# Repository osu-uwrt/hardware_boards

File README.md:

# riptide_hardware
Riptide specific EAGLE libs and board files

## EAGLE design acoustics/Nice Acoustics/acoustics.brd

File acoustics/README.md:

# riptide_hardware
Acoustics board.

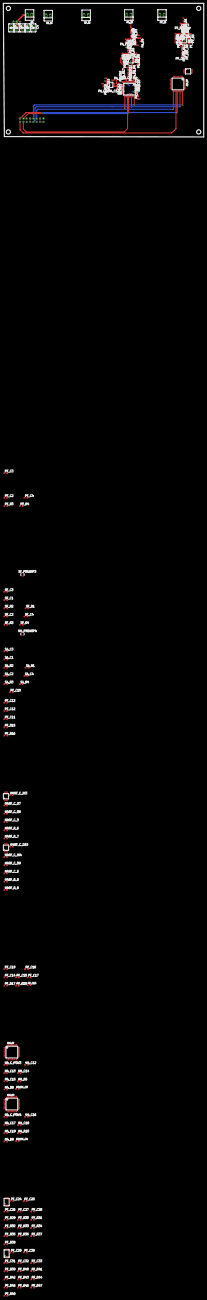
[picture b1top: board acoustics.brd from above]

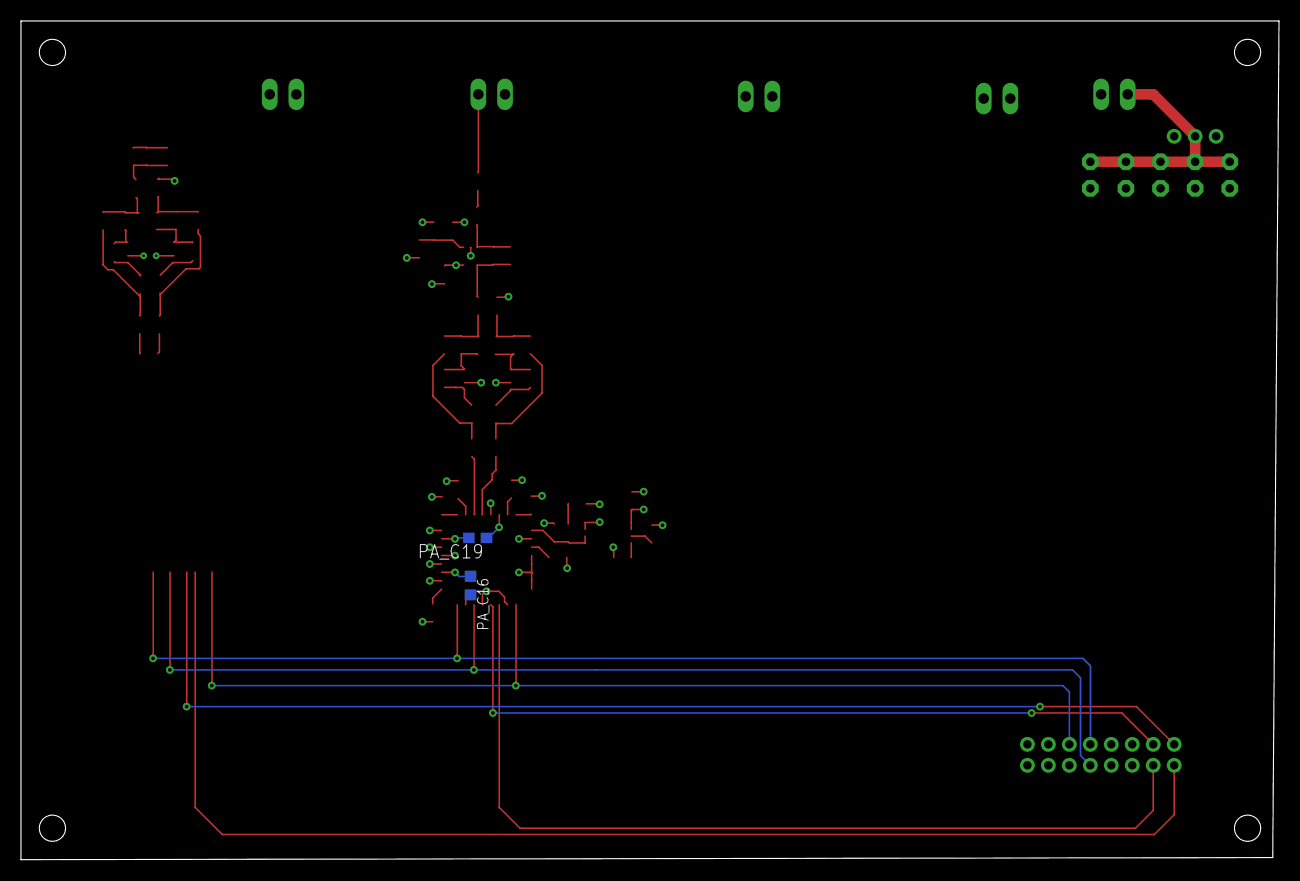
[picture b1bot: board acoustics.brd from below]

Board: 4 copper layers, 120.0 x 80.0 mm, 176 parts (2 on the bottom side), 114 nets.

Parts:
ADC_H7, ADC_H8: ADS8322; TQFP-32
ADC_PA: ADS8322; TQFP-32
ADC_PF: ADS8322; TQFP-32
C1, C2, C3, C4, C5: C2.5-3
H4ADC_C3, H4ADC_C4: 1uf; C0603K
H4RF_C_3, H4RF_C_5, H4_C12, H4_C13, H4_C14, H4_C15, H4_C16, H4_C17, H4_C18, H4_C19, H4_C_POW3, H4_C_POW4: 1uf; C0603
H4RF_C_IN3, H4RF_C_IN4: 10uf; C0603
H4RF_C_O7, H4RF_C_O9: 0.1uf; C0603
H4RF_C_O8, H4RF_C_O10: 47uf; C0603
H4RF_R_6, H4RF_R_8: 121k; R0603
H4RF_R_7, H4RF_R_9: 47m; R0603
H4_PREAMP4: TLV6741; SC70-5
H4_R5, H4_R9: 60.4k; R0603
H4_R8, H4_R10: 10K; R0603
H4_REFGEN3, H4_REFGEN4: REF6025
P1: 22-23-2021
PA_C1: 1pF; C0603
PA_C2: 5nF; C0603
PA_C3: 10mF; C0603
PA_C4: 100nF; C0603
PA_C5, PA_C9: 270pF; C0603
PA_C6: 470 pF; C0603
PA_C7: 1nF; C0603
PA_C8: 22nF; C0603
PA_C10: 10uf; C0603
PA_C11, PA_C14, PA_C15, PA_C17, PA_C18, PA_C19: 1uf; C0603
PA_C12: 47uf; C0603
PA_C13: 0.1uf; C0603
PA_C16: 1uf; C0603K
PA_DA: THS4551; VSSOP-8
PA_IN: 22-23-2021
PA_PREAMP: TLV6741; SC70-5
PA_R1: 10k; R0603
PA_R2: 1 M; R0603
PA_R3, PA_R4: 100k; R0603
PA_R5, PA_R10, PA_R14: 1.2k; R0603
PA_R6: 1.2K; R0603
PA_R7, PA_R11: 330; R0603
PA_R8, PA_R12: 5; R0603
PA_R9, PA_R13: 10; R0603
PA_R15: 121k; R0603
PA_R16: 47m; R0603
PA_R17: 60.4k; R0603
PA_R18: 10K; R0603
PA_REFGEN: REF6025
PF_C1: 1pF; C0603
PF_C2: 5nF; C0603
PF_C3: 10mF; C0603
PF_C4: 100nF; C0603
PF_C5, PF_C9, PF_C24, PF_C25, PF_C29, PF_C30: 270pF; C0603
PF_C6, PF_C27, PF_C32: 470 pF; C0603
PF_C7, PF_C26, PF_C31: 1nF; C0603
PF_C8, PF_C28, PF_C33: 22nF; C0603
PF_C10: 10uf; C0603
PF_C11, PF_C14, PF_C15, PF_C17, PF_C18, PF_C19: 1uf; C0603
PF_C12: 47uf; C0603
PF_C13: 0.1uf; C0603
PF_C16: 1uf; C0603K
PF_DA, PF_DA2, PF_DA3: THS4551; VSSOP-8
PF_IN: 22-23-2021
PF_PREAMP: TLV6741; SC70-5
PF_R1: 10k; R0603
PF_R2: 1 M; R0603
PF_R3, PF_R4: 100k; R0603
PF_R5, PF_R10, PF_R14, PF_R31, PF_R35, PF_R36, PF_R41, PF_R45, PF_R46: 1.2k; R0603
PF_R6, PF_R30, PF_R40: 1.2K; R0603
PF_R7, PF_R11, PF_R29, PF_R32, PF_R39, PF_R42: 330; R0603
PF_R8, PF_R12, PF_R33, PF_R34, PF_R43, PF_R44: 5; R0603
PF_R9, PF_R13, PF_R37, PF_R38, PF_R47, PF_R48: 10; R0603
PF_R15: 121k; R0603
PF_R16: 47m; R0603
PF_R17: 60.4k; R0603
PF_R18: 10K; R0603
PF_REFGEN: REF6025
SA_C1: 1pF; C0603
SA_C2: 5nF; C0603
SA_C3: 10mF; C0603
SA_C4: 100nF; C0603
SA_IN: 22-23-2021
SA_R1: 10k; R0603
SA_R2: 1 M; R0603
SA_R3, SA_R4: 100k; R0603
SF_C1: 1pF; C0603
SF_C2: 5nF; C0603
SF_C3: 10mF; C0603
SF_C4: 100nF; C0603
SF_IN: 22-23-2021
SF_PREAMP3: TLV6741; SC70-5
SF_R1: 10k; R0603
SF_R2: 1 M; R0603
SF_R3, SF_R4: 100k; R0603
U$1: 1X3
U$2: 2X8

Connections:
+3V3: ADC_H7.6, ADC_H7.27, ADC_H7.28, ADC_H7.29, ADC_H7.32, ADC_H8.6, ADC_H8.27, ADC_H8.28, ADC_H8.29, ADC_H8.32, ADC_PA.6, ADC_PA.27, ADC_PA.28, ADC_PA.29, ADC_PA.32, ADC_PF.6, ADC_PF.27, ADC_PF.28, ADC_PF.29, ADC_PF.32, H4ADC_C3.1, H4ADC_C4.1, H4RF_C_IN3.2, H4RF_C_IN4.2, H4_C_POW3.1, H4_C_POW4.1, H4_PREAMP4.5, H4_REFGEN3.1, H4_REFGEN3.2, H4_REFGEN4.1, H4_REFGEN4.2, PA_C4.2, PA_C10.2, PA_C16.1, PA_C19.1, PA_DA.3, PA_PREAMP.5, PA_R4.2, PA_REFGEN.1, PA_REFGEN.2, PF_C4.2, PF_C10.2, PF_C16.1, PF_C19.1, PF_DA.3, PF_DA2.3, PF_DA3.3, PF_PREAMP.5, PF_R4.2, PF_REFGEN.1, PF_REFGEN.2, SA_C4.2, SA_R4.2, SF_C4.2, SF_PREAMP3.5, SF_R4.2, U$1.1
+5V: C1.1, C2.1, C3.1, C4.1, C5.1, P1.2, U$1.2
AMPED_PA: PA_C1.2, PA_PREAMP.4, PA_R2.2, PA_R6.1
AMPED_PF: PF_C1.2, PF_PREAMP.4, PF_R2.2, PF_R6.1
AMPED_SA: H4_PREAMP4.4, PF_R40.1, SA_C1.2, SA_R2.2
AMPED_SF: PF_R30.1, SF_C1.2, SF_PREAMP3.4, SF_R2.2
CLK: ADC_H7.24, ADC_H8.24, ADC_PA.24, ADC_PF.24, U$2.10
DIFF_N_PA: ADC_PA.3, PA_C8.1, PA_R9.2
DIFF_N_PF: ADC_PF.3, PF_C8.1, PF_R9.2
DIFF_N_SA: ADC_H8.3, PF_C33.1, PF_R47.2
DIFF_N_SF: ADC_H7.3, PF_C28.1, PF_R37.2
DIFF_P_PA: ADC_PA.4, PA_C8.2, PA_R13.2
DIFF_P_PF: ADC_PF.4, PF_C8.2, PF_R13.2
DIFF_P_SA: ADC_H8.4, PF_C33.2, PF_R48.2
DIFF_P_SF: ADC_H7.4, PF_C28.2, PF_R38.2
DOUT_PA: ADC_PA.20, U$2.4
DOUT_PF: ADC_PF.20, U$2.2
DOUT_SA: ADC_H8.20, U$2.8
DOUT_SF: ADC_H7.20, U$2.6
DRDY_PA: ADC_PA.19, U$2.3
DRDY_PF: ADC_PF.19, U$2.1
DRDY_SA: ADC_H8.19, U$2.7
DRDY_SF: ADC_H7.19, U$2.5
GND: ADC_H7.5, ADC_H7.10, ADC_H7.12, ADC_H7.13, ADC_H7.14, ADC_H7.15, ADC_H7.16, ADC_H7.18, ADC_H7.21, ADC_H7.23, ADC_H7.26, ADC_H7.30, ADC_H7.31, ADC_H8.5, ADC_H8.10, ADC_H8.12, ADC_H8.13, ADC_H8.14, ADC_H8.15, ADC_H8.16, ADC_H8.18, ADC_H8.21, ADC_H8.23, ADC_H8.26, ADC_H8.30, ADC_H8.31, ADC_PA.5, ADC_PA.10, ADC_PA.12, ADC_PA.13, ADC_PA.14, ADC_PA.15, ADC_PA.16, ADC_PA.18, ADC_PA.21, ADC_PA.23, ADC_PA.26, ADC_PA.30, ADC_PA.31, ADC_PF.5, ADC_PF.10, ADC_PF.12, ADC_PF.13, ADC_PF.14, ADC_PF.15, ADC_PF.16, ADC_PF.18, ADC_PF.21, ADC_PF.23, ADC_PF.26, ADC_PF.30, ADC_PF.31, C1.2, C2.2, C3.2, C4.2, C5.2, H4ADC_C3.2, H4ADC_C4.2, H4RF_C_3.1, H4RF_C_5.1, H4RF_C_IN3.1, H4RF_C_IN4.1, H4RF_C_O7.1, H4RF_C_O9.1, H4RF_R_6.1, H4RF_R_7.1, H4RF_R_8.1, H4RF_R_9.1, H4_C12.1, H4_C13.1, H4_C14.2, H4_C15.1, H4_C16.1, H4_C17.1, H4_C18.2, H4_C19.1, H4_C_POW3.2, H4_C_POW4.2, H4_PREAMP4.2, H4_R5.2, H4_R8.2, H4_R9.2, H4_R10.2, H4_REFGEN3.7, H4_REFGEN3.8, H4_REFGEN4.7, H4_REFGEN4.8, P1.1, PA_C3.2, PA_C4.1, PA_C10.1, PA_C11.1, PA_C13.1, PA_C14.1, PA_C15.1, PA_C16.2, PA_C17.2, PA_C18.1, PA_C19.2, PA_DA.6, PA_IN.2, PA_PREAMP.2, PA_R3.2, PA_R10.1, PA_R15.1, PA_R16.1, PA_R17.2, PA_R18.2, PA_REFGEN.7, PA_REFGEN.8, PF_C3.2, PF_C4.1, PF_C10.1, PF_C11.1, PF_C13.1, PF_C14.1, PF_C15.1, PF_C16.2, PF_C17.2, PF_C18.1, PF_C19.2, PF_DA.6, PF_DA2.6, PF_DA3.6, PF_IN.2, PF_PREAMP.2, PF_R3.2, PF_R10.1, PF_R15.1, PF_R16.1, PF_R17.2, PF_R18.2, PF_R31.1, PF_R41.1, PF_REFGEN.7, PF_REFGEN.8, SA_C3.2, SA_C4.1, SA_IN.2, SA_R3.2, SF_C3.2, SF_C4.1, SF_IN.2, SF_PREAMP3.2, SF_R3.2, U$1.3, U$2.15, U$2.16
unnamed: PA_C5.2, PA_DA.5, PA_R8.1
unnamed: PA_C5.1, PA_C7.1, PA_DA.8, PA_R7.2
unnamed: PA_C7.2, PA_C9.1, PA_DA.1, PA_R11.2
unnamed: PA_C6.1, PA_R5.1, PA_R6.2, PA_R7.1
unnamed: PA_C6.2, PA_R10.2, PA_R11.1, PA_R14.1
unnamed: PA_C9.2, PA_DA.4, PA_R12.1
unnamed: PA_R5.2, PA_R8.2, PA_R9.1
unnamed: PA_R12.2, PA_R13.1, PA_R14.2
unnamed: PF_C24.2, PF_DA2.5, PF_R33.1
unnamed: PF_C24.1, PF_C26.1, PF_DA2.8, PF_R29.2
unnamed: PF_C25.1, PF_C26.2, PF_DA2.1, PF_R32.2
unnamed: PF_C27.1, PF_R29.1, PF_R30.2, PF_R35.1
unnamed: PF_C27.2, PF_R31.2, PF_R32.1, PF_R36.1
unnamed: PF_C25.2, PF_DA2.4, PF_R34.1
unnamed: PF_R33.2, PF_R35.2, PF_R37.1
unnamed: PF_R34.2, PF_R36.2, PF_R38.1
unnamed: PF_C29.2, PF_DA3.5, PF_R43.1
unnamed: PF_C29.1, PF_C31.1, PF_DA3.8, PF_R39.2
unnamed: PF_C30.1, PF_C31.2, PF_DA3.1, PF_R42.2
unnamed: PF_C32.1, PF_R39.1, PF_R40.2, PF_R45.1
unnamed: PF_C32.2, PF_R41.2, PF_R42.1, PF_R46.1
unnamed: PF_C30.2, PF_DA3.4, PF_R44.1
unnamed: PF_R43.2, PF_R45.2, PF_R47.1
unnamed: PF_R44.2, PF_R46.2, PF_R48.1
unnamed: PF_R12.2, PF_R13.1, PF_R14.2
unnamed: PF_C5.2, PF_DA.5, PF_R8.1
unnamed: PF_C5.1, PF_C7.1, PF_DA.8, PF_R7.2
unnamed: PF_C7.2, PF_C9.1, PF_DA.1, PF_R11.2
unnamed: PF_C6.1, PF_R5.1, PF_R6.2, PF_R7.1
unnamed: PF_C6.2, PF_R10.2, PF_R11.1, PF_R14.1
unnamed: PF_C9.2, PF_DA.4, PF_R12.1
unnamed: PF_C11.2, PF_REFGEN.4
unnamed: PF_R15.2, PF_REFGEN.3
unnamed: PF_C12.1, PF_R16.2
unnamed: PF_R5.2, PF_R8.2, PF_R9.1
unnamed: PA_C11.2, PA_REFGEN.4
unnamed: PA_R15.2, PA_REFGEN.3
unnamed: PA_C12.1, PA_R16.2
unnamed: H4RF_C_3.2, H4_REFGEN3.4
unnamed: H4RF_R_6.2, H4_REFGEN3.3
unnamed: H4RF_C_O8.1, H4RF_R_7.2
unnamed: H4RF_C_5.2, H4_REFGEN4.4
unnamed: H4RF_R_8.2, H4_REFGEN4.3
unnamed: H4RF_C_O10.1, H4RF_R_9.2
unnamed: ADC_PF.2, PF_C14.2
unnamed: PF_C2.2, PF_R1.1
unnamed: PF_C1.1, PF_PREAMP.3, PF_R1.2, PF_R2.1
unnamed: PF_C3.1, PF_PREAMP.1, PF_R3.1, PF_R4.1
unnamed: ADC_PA.1, PA_C15.2
unnamed: PA_C2.2, PA_R1.1
unnamed: PA_C1.1, PA_PREAMP.3, PA_R1.2, PA_R2.1
unnamed: PA_C3.1, PA_PREAMP.1, PA_R3.1, PA_R4.1
unnamed: ADC_PA.8, PA_R18.1
unnamed: SF_C2.2, SF_R1.1
unnamed: SF_C1.1, SF_PREAMP3.3, SF_R1.2, SF_R2.1
unnamed: SF_C3.1, SF_PREAMP3.1, SF_R3.1, SF_R4.1
unnamed: ADC_PA.7, PA_R17.1
unnamed: SA_C2.2, SA_R1.1
unnamed: H4_PREAMP4.3, SA_C1.1, SA_R1.2, SA_R2.1
unnamed: H4_PREAMP4.1, SA_C3.1, SA_R3.1, SA_R4.1
unnamed: ADC_PA.11, PA_C17.1
unnamed: ADC_PA.25, PA_C18.2
unnamed: ADC_PF.1, PF_C15.2
unnamed: ADC_PA.2, PA_C14.2
unnamed: ADC_PF.8, PF_R18.1
unnamed: ADC_PF.7, PF_R17.1
unnamed: ADC_PF.11, PF_C17.1
unnamed: ADC_PF.25, PF_C18.2
unnamed: ADC_H7.1, H4_C13.2
unnamed: ADC_H7.8, H4_R8.1
unnamed: ADC_H7.7, H4_R5.1
unnamed: ADC_H7.11, H4_C14.1
unnamed: ADC_H7.25, H4_C15.2
unnamed: ADC_H7.2, H4_C12.2
unnamed: ADC_H8.1, H4_C17.2
unnamed: ADC_H8.8, H4_R10.1
unnamed: ADC_H8.7, H4_R9.1
unnamed: ADC_H8.11, H4_C18.1
unnamed: ADC_H8.25, H4_C19.2
unnamed: ADC_H8.2, H4_C16.2
RAW_PA: PA_C2.1, PA_IN.1
RAW_PF: PF_C2.1, PF_IN.1
RAW_SA: SA_C2.1, SA_IN.1
RAW_SF: SF_C2.1, SF_IN.1
REF_PA: ADC_PA.9, PA_C12.2, PA_C13.2, PA_REFGEN.5, PA_REFGEN.6
REF_PF: ADC_PF.9, PF_C12.2, PF_C13.2, PF_REFGEN.5, PF_REFGEN.6
REF_SA: ADC_H8.9, H4RF_C_O9.2, H4RF_C_O10.2, H4_REFGEN4.5, H4_REFGEN4.6
REF_SF: ADC_H7.9, H4RF_C_O7.2, H4RF_C_O8.2, H4_REFGEN3.5, H4_REFGEN3.6
SCLK: ADC_H7.22, ADC_H8.22, ADC_PA.22, ADC_PF.22, U$2.9
START: ADC_H7.17, ADC_H8.17, ADC_PA.17, ADC_PF.17, U$2.12

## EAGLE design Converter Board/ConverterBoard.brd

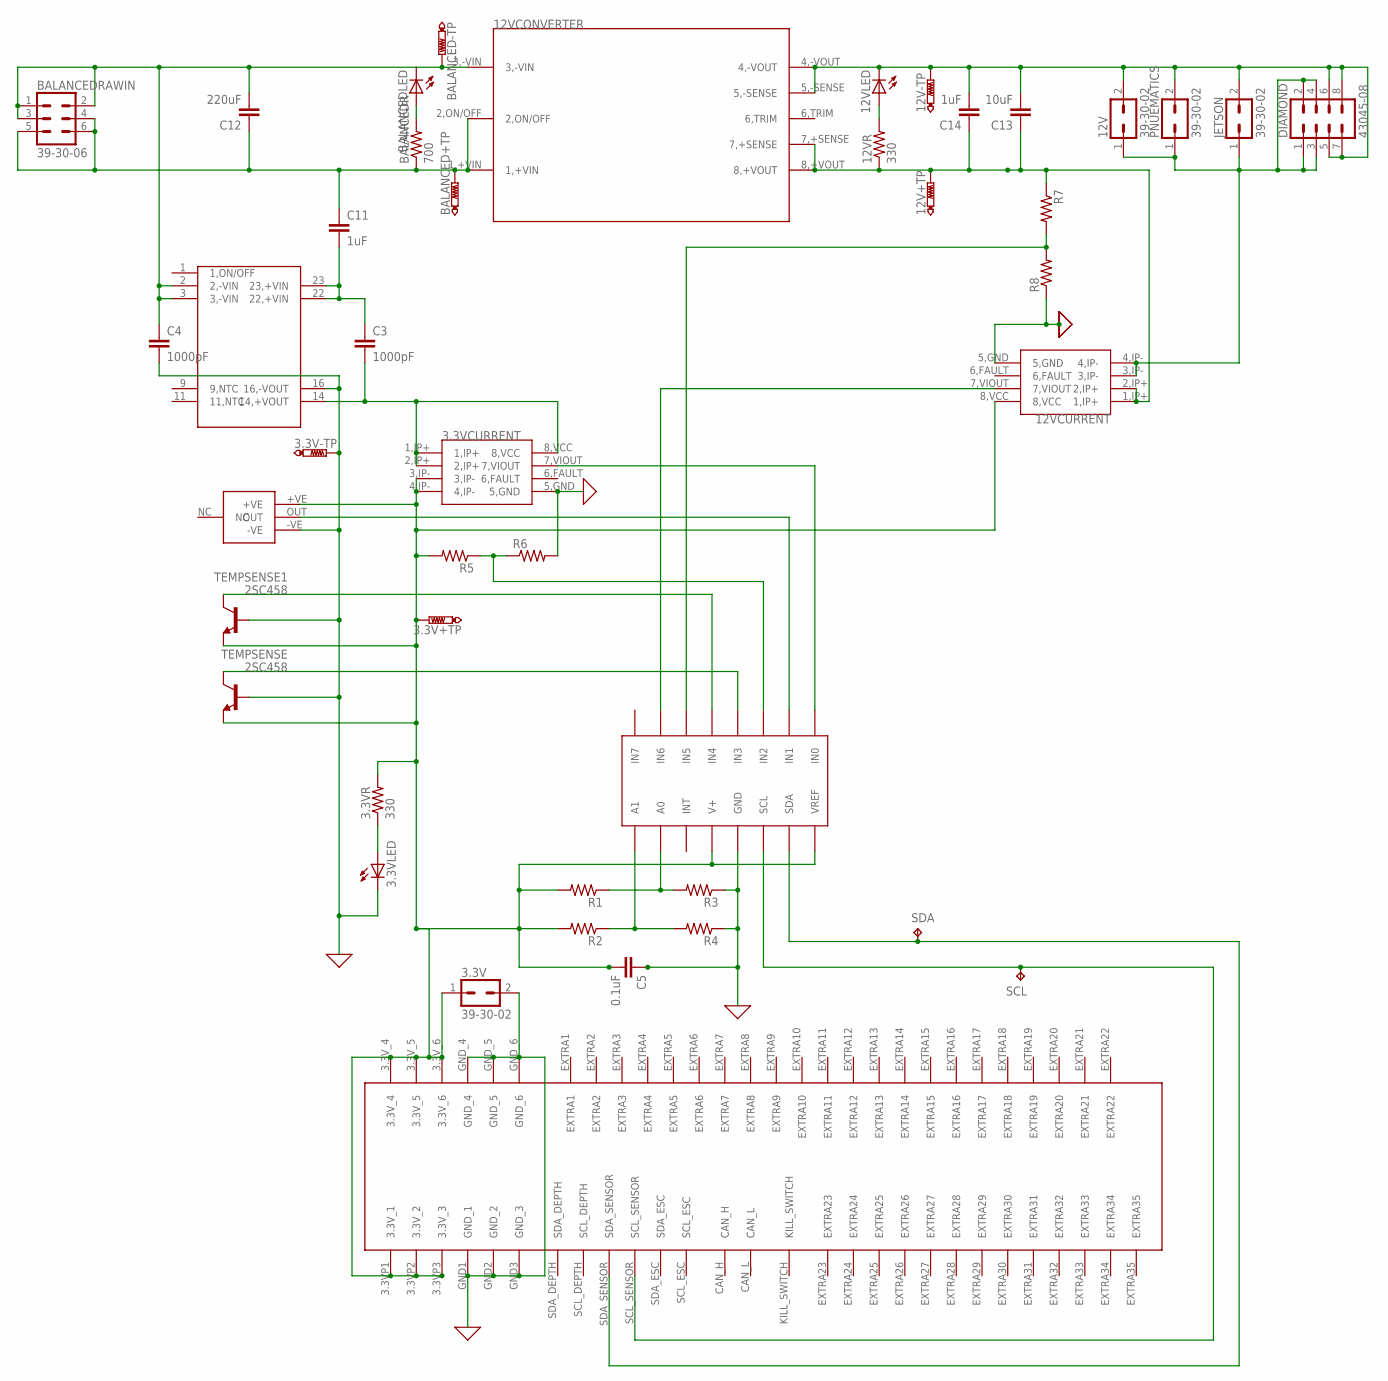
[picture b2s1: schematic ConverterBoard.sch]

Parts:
3.3V, 12V: 39-30-02; 39-30-?02?
3.3V+TP, 3.3V-TP, 12V+TP, 12V-TP: PTR1B1,27; B1,27
3.3VCURRENT, 12VCURRENT: CURRENTSENS
3.3VLED, 12VLED: LTST-S270GKT
3.3VR, 12VR: 330; 0204/7
12VCONVERTER: 12VCONV
ADC: ADC128D818; TSSOP-16
BALANCED+TP: PTR1B1,27; B1,27
BALANCED-TP: PTR1B1,27; B1,27
BALANCEDLED: LTST-S270GKT
BALANCEDR: 700; 0204/7
BALANCEDRAWIN: 39-30-06; 39-30-?06?
C3, C4: 1000pF; C5B3
C5: 0.1uF; C2.5-2
C11, C14: 1uF; C5B3
C12: 220uF; C5B3
C13: 10uF; C5B3
DIAMOND: 43045-08
JETSON: 39-30-02; 39-30-?02?
PNUEMATICS: 39-30-02; 39-30-?02?
R1, R2, R3, R4, R5, R6, R7, R8: R-US_0204/7; 0204/7
SCL: TPPAD1-20; P1-20
SDA: TPPAD1-20; P1-20
TEMPSENSE, TEMPSENSE1: 2SC458; TO92-ECB
U$2: 3.3VCONV
U$3: 5530843; 5530843-6-BOARDFINGERS
U$6: HUMIDITYSENSOR

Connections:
3.3VCONVIN: C3.1, C11.2, U$2.22 (22,+VIN), U$2.23 (23,+VIN)
3.3VCONVOUT: 3.3VCURRENT.1,IP+, 3.3VCURRENT.2,IP+, 3.3VCURRENT.8,VCC, C3.2, U$2.14 (14,+VOUT)
3.3VCURRENTDATA: 3.3VCURRENT.7,VIOUT, ADC.IN0
3.3VCURRENTOUT: 3.3V.1, 3.3V+TP.TP, 3.3VCURRENT.3,IP-, 3.3VCURRENT.4,IP-, 3.3VR.2, 12VCURRENT.8,VCC, ADC.V+, ADC.VREF, C5.2, R1.2, R2.2, R5.2, TEMPSENSE.E, TEMPSENSE1.E, U$3.3.3VP1 (3.3V_1), U$3.3.3VP2 (3.3V_2), U$3.3.3VP3 (3.3V_3), U$3.3.3V_4, U$3.3.3V_5, U$3.3.3V_6, U$6.+VE
3.3VDATA: ADC.IN2, R5.1, R6.1
3.3VLED: 3.3VLED.ANODE (A), 3.3VR.1
12VCONV+: 12V+TP.TP, 12VCONVERTER.7,+SENSE, 12VCONVERTER.8,+VOUT, 12VCURRENT.1,IP+, 12VCURRENT.2,IP+, 12VR.1, C13.1, C14.1, R7.1
12VCURRENTDATA: 12VCURRENT.7,VIOUT, ADC.IN6
12VCURRENTOUT: 12V.1, 12VCURRENT.3,IP-, 12VCURRENT.4,IP-, DIAMOND.1, DIAMOND.2, DIAMOND.3, DIAMOND.4, JETSON.1, PNUEMATICS.1
12VDIV: ADC.IN5, R7.2, R8.2
12VLED: 12VLED.ANODE (A), 12VR.2
A0: ADC.A0, R1.1, R3.2
A1: ADC.A1, R2.1, R4.2
BALANCED+: 12VCONVERTER.1,+VIN, 12VCONVERTER.2,ON/OFF, BALANCED+TP.TP, BALANCEDR.1, BALANCEDRAWIN.4, BALANCEDRAWIN.5, BALANCEDRAWIN.6, C11.1, C12.1
BALANCEDGND: 12VCONVERTER.3,-VIN, BALANCED-TP.TP, BALANCEDLED.CATHODE (C), BALANCEDRAWIN.1, BALANCEDRAWIN.2, BALANCEDRAWIN.3, C4.1, C12.2, U$2.2 (2,-VIN), U$2.3 (3,-VIN)
BALANCEDLED: BALANCEDLED.ANODE (A), BALANCEDR.2
CMGND: 3.3V.2, 3.3V-TP.TP, 3.3VCURRENT.5,GND, 3.3VLED.CATHODE (C), 12V.2, 12V-TP.TP, 12VCONVERTER.4,-VOUT, 12VCONVERTER.5,-SENSE, 12VCURRENT.5,GND, 12VLED.CATHODE (C), ADC.GND, C4.2, C5.1, C13.2, C14.2, DIAMOND.5, DIAMOND.6, DIAMOND.7, DIAMOND.8, JETSON.2, PNUEMATICS.2, R3.1, R4.1, R6.2, R8.1, TEMPSENSE.B, TEMPSENSE1.B, U$2.16 (16,-VOUT), U$3.GND1 (GND_1), U$3.GND2 (GND_2), U$3.GND3 (GND_3), U$3.GND_4, U$3.GND_5, U$3.GND_6, U$6.-VE
HUMIDITYDATA: ADC.IN1, U$6.OUT
SCL: ADC.SCL, SCL.TP, U$3.SCL_SENSOR
SDA: ADC.SDA, SDA.TP, U$3.SDA_SENSOR
TEMP1DATA: ADC.IN4, TEMPSENSE1.C
TEMPDATA: ADC.IN3, TEMPSENSE.C

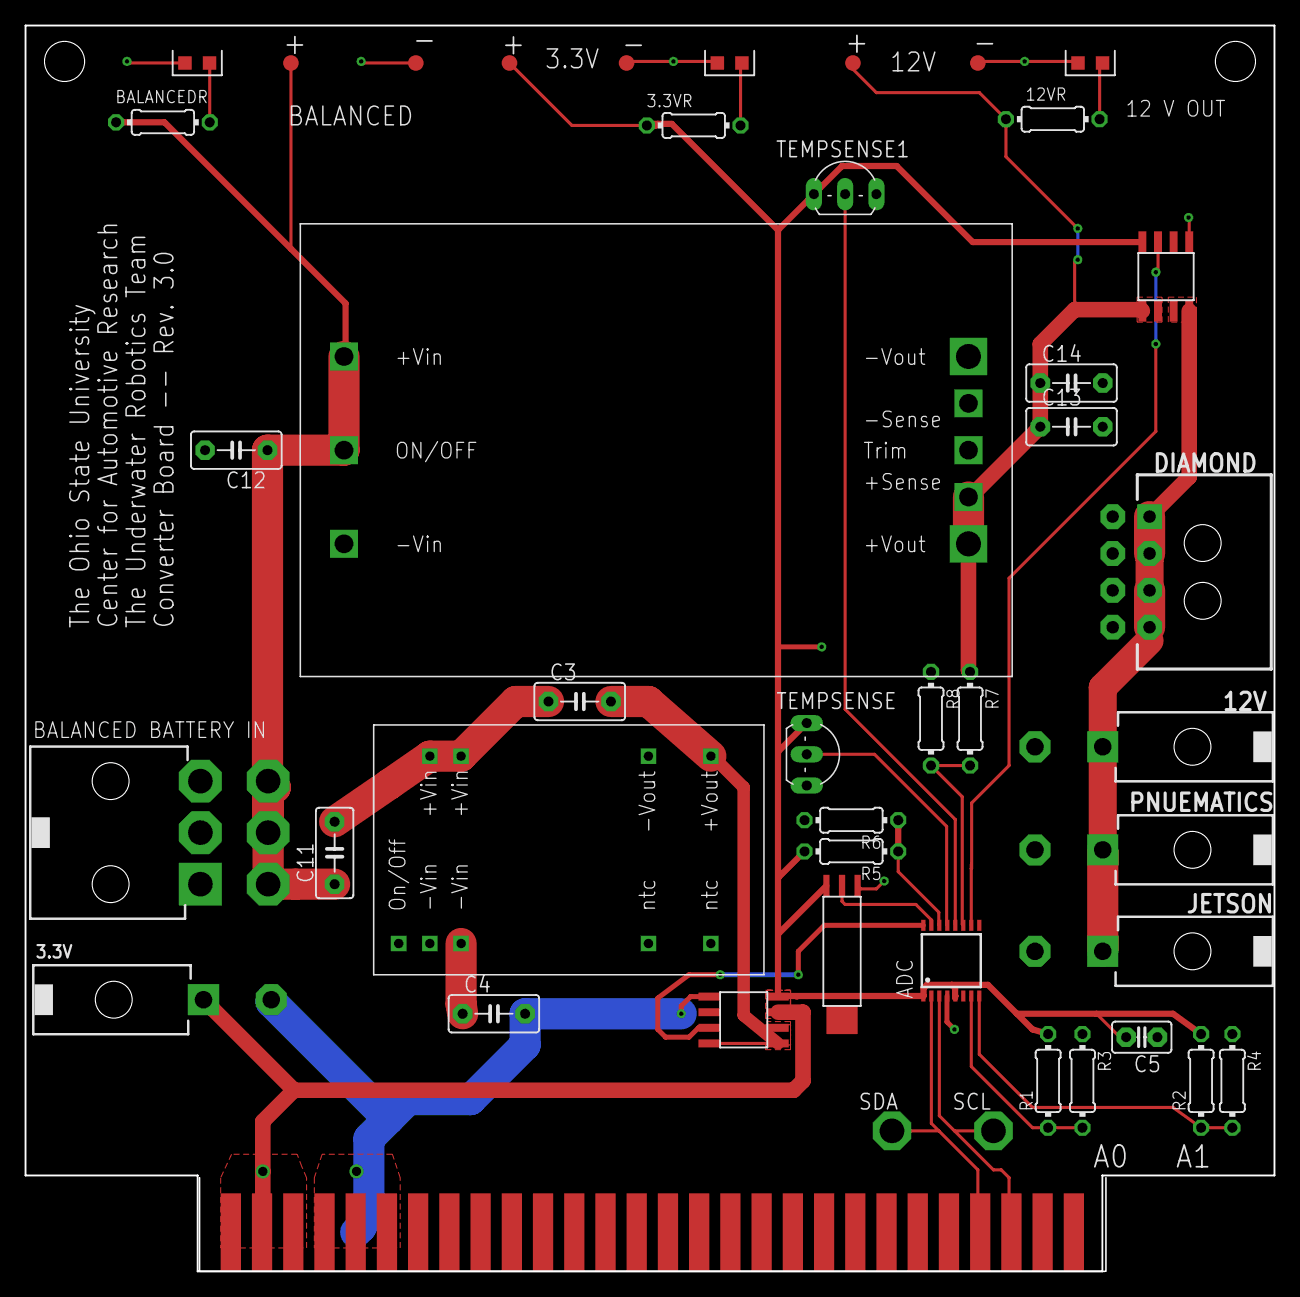
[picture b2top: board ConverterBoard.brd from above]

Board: 2 copper layers, 101.6 x 101.3 mm, 44 parts (0 on the bottom side), 22 nets.

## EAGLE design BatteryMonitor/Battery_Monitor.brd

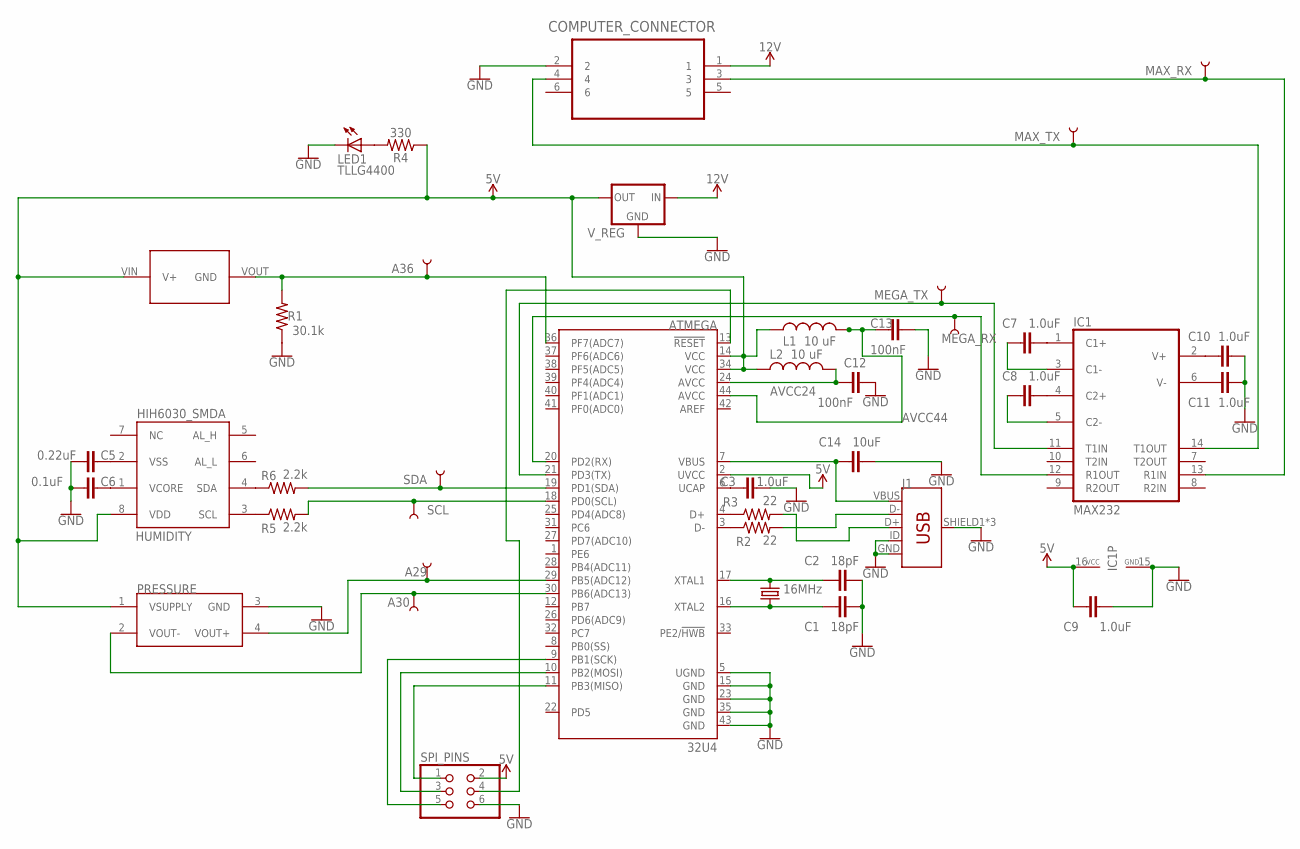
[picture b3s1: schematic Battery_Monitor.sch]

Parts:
16MHZ_CRYSTAL: 16MHz; HC49/S
A29, A30, A36: TEST-POINT3X5; PAD.03X.05
ATMEGA: 32U4; QFN-44
C1, C2: 18pF; 0603
C3, C7, C8, C9, C10, C11: 1.0uF; 0402
C5: 0.22uF; 0603
C6: 0.1uF; 0402
C12, C13: 100nF; 0402
C14: 10uF; 0603
COMPUTER_CONNECTOR: 52271-0469; MOLEX_52271-0469
FLEX_SQ: MOLEX_2WIRE2018; SMT_MOLEX_PKG
HUMIDITY: HIH6030_SMDA; SMD-8
IC1: MAX232; DIL16
J1: USB_MICRO-B_FEMALE-SMT; USB-B-MICRO-SMD
L1, L2: 10 uF; L1812
LED1: TLLG4400; LED3MM
MAX_RX: TEST-POINT3X5; PAD.03X.05
MAX_TX: TEST-POINT3X5; PAD.03X.05
MEGA_RX: TEST-POINT3X5; PAD.03X.05
MEGA_TX: TEST-POINT3X5; PAD.03X.05
PRESSURE: HONEYWELL_PRESSURE_SENSOR2018; 4PIN_SMT
R1: 30.1k; 0603
R2, R3: 22; 0402
R4: 330; 0603
R5, R6: 2.2k; 0603
SCL: TEST-POINT3X5; PAD.03X.05
SDA: TEST-POINT3X5; PAD.03X.05
SPI_PINS: PINHD-2X3; 2X03
V_REG: DC_DC_78XXA; DC-DC_CONVERTER_78XX

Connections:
5V: ATMEGA.2 (UVCC), ATMEGA.14 (VCC), ATMEGA.34 (VCC), C9.1, FLEX_SQ.VIN (V+), HUMIDITY.8 (VDD), IC1.16 (VCC), L1.1, L2.1, PRESSURE.1 (VSUPPLY), R4.1, SPI_PINS.2, V_REG.VOUT (OUT)
12V: COMPUTER_CONNECTOR.1, V_REG.VIN (IN)
A29: A29.P$1, ATMEGA.29 (PB5(ADC12)), PRESSURE.4 (VOUT+)
A30: A30.P$1, ATMEGA.30 (PB6(ADC13)), PRESSURE.2 (VOUT-)
A36: A36.P$1, ATMEGA.36 (PF7(ADC7)), FLEX_SQ.VOUT (GND), R1.2
AVCC24: ATMEGA.24 (AVCC), C12.2, L2.2
AVCC44: ATMEGA.44 (AVCC), C13.2, L1.2
D+: J1.D+, R3.2
D-: J1.D-, R2.2
GND: ATMEGA.5 (UGND), ATMEGA.15 (GND), ATMEGA.23 (GND), ATMEGA.35 (GND), ATMEGA.43 (GND), C1.1, C2.1, C3.2, C5.1, C6.1, C9.2, C10.2, C11.2, C12.1, C13.1, C14.2, COMPUTER_CONNECTOR.2, IC1.15 (GND), J1.GND, J1.ID, J1.SHIELD1 (SHIELD), J1.SHIELD2 (SHIELD), J1.SHIELD3 (SHIELD), LED1.K (C), PRESSURE.3 (GND), R1.1, SPI_PINS.6, V_REG.GND
MAX_RX: COMPUTER_CONNECTOR.3, IC1.13 (R1IN), MAX_RX.P$1
MAX_TX: COMPUTER_CONNECTOR.4, IC1.14 (T1OUT), MAX_TX.P$1
MEGA_RX: ATMEGA.20 (PD2(RX)), IC1.12 (R1OUT), MEGA_RX.P$1
MEGA_TX: ATMEGA.21 (PD3(TX)), IC1.11 (T1IN), MEGA_TX.P$1
MISO: ATMEGA.11 (PB3(MISO)), SPI_PINS.1
MOSI: ATMEGA.10 (PB2(MOSI)), SPI_PINS.3
unnamed: HUMIDITY.3 (SCL), R5.1
unnamed: HUMIDITY.4 (SDA), R6.1
unnamed: C6.2, HUMIDITY.1 (VCORE)
unnamed: C5.2, HUMIDITY.2 (VSS)
unnamed: C7.1, IC1.1 (C1+)
unnamed: C8.1, IC1.4 (C2+)
unnamed: C8.2, IC1.5 (C2-)
unnamed: C7.2, IC1.3 (C1-)
unnamed: C10.1, IC1.2 (V+)
unnamed: C11.1, IC1.6 (V-)
unnamed: ATMEGA.3 (D-), R2.1
unnamed: ATMEGA.4 (D+), R3.1
unnamed: ATMEGA.6 (UCAP), C3.1
unnamed: LED1.A, R4.2
RESET: ATMEGA.13 (!RESET), SPI_PINS.4
SCK: ATMEGA.9 (PB1(SCK)), SPI_PINS.5
SCL: ATMEGA.18 (PD0(SCL)), R5.2, SCL.P$1
SDA: ATMEGA.19 (PD1(SDA)), R6.2, SDA.P$1
TAL1: 16MHZ_CRYSTAL.1, ATMEGA.17 (XTAL1), C2.2
TAL2: 16MHZ_CRYSTAL.2, ATMEGA.16 (XTAL2), C1.2
VBUS: ATMEGA.7 (VBUS), C14.1, J1.VBUS

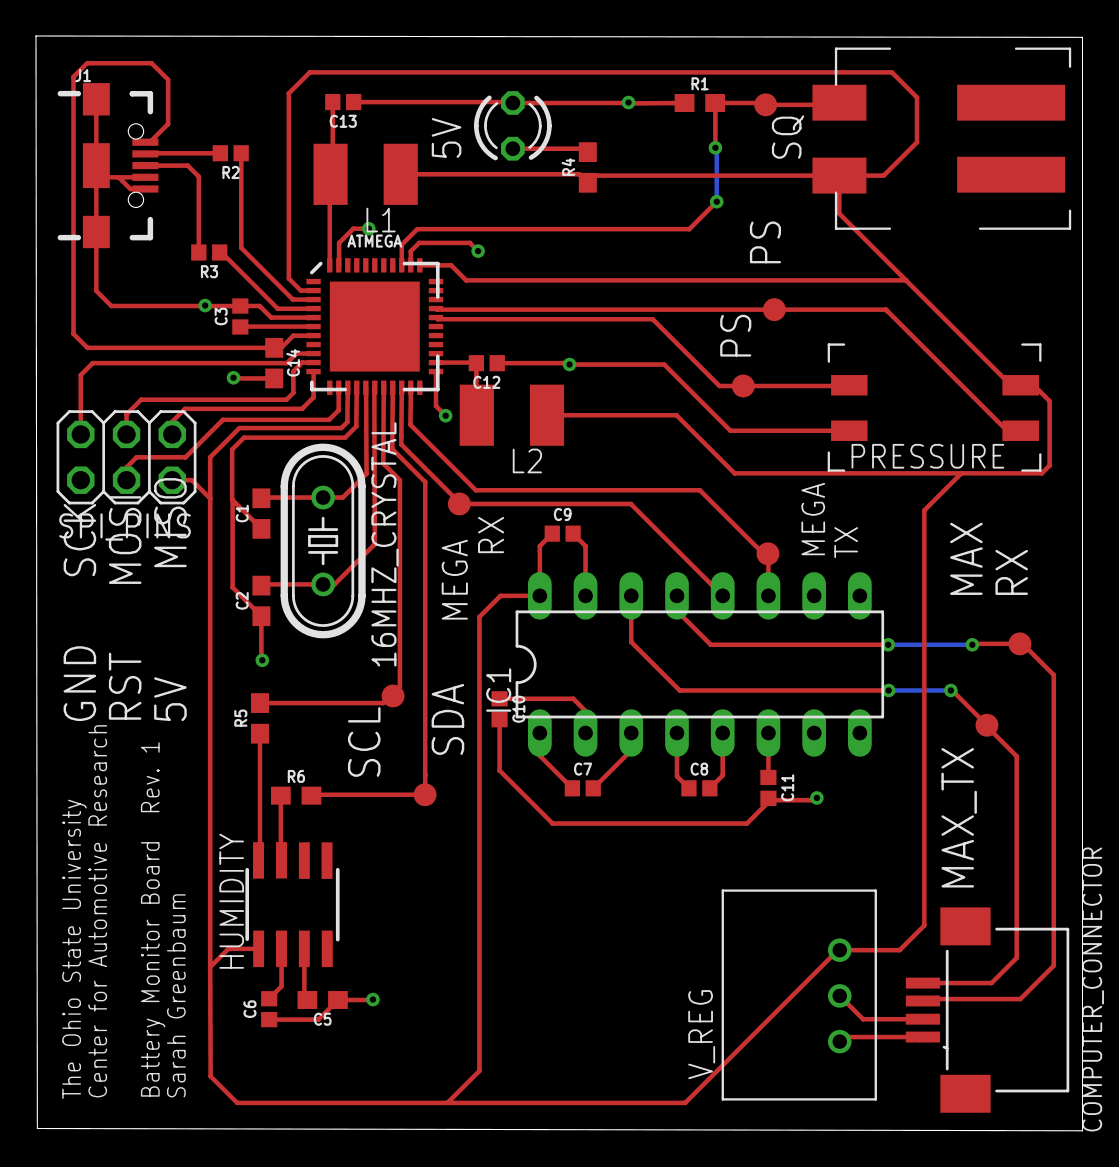
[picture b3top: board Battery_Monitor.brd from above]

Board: 2 copper layers, 58.1 x 60.8 mm, 41 parts (0 on the bottom side), 37 nets.

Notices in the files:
parts and their libraries:
SparkFun-IC-Power: Licensing: Creative Commons ShareAlike 4.0 International - https://creativecommons.org/licenses/by-sa/4.0
con-molex-mini-fit: Copyright (C) 2011, Bob Starr
